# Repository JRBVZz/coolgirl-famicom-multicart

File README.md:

# COOLGIRL - ultimate multigame cartridge for Famicom

The goal of the project is to create a open source Famicom cartridge that will not be too expensive and can contain up to ~700 games of various mappers.

It's inspired by ultra cheap "COOLBOY" multicarts but instead of using single mapper (MMC3) "COOLGIRL" uses EPM1270T144 CPLD chip to simulate many different mappers. Both PRG and CHR data stored on a single flash memory chip. Before game starts loader loads CHR data from flash to CHR RAM and sets PRG offset, banking modes, mapper code and other settings via registers. There is lockout register bit which prevents further writes.

Full characteristics:
* PRG ROM: up to 128 MiB
* CHR RAM: up to 512 KiB
* PRG RAM: 32 KiB, non-volatile (FRAM) (optional)

--> You can use FRAM or SRAM with Battery. If you select FRAM (18W08 or 18L08), just solder jumper "FRAM". With SRAM (e.g. CY62256VLL)+Battery you need solder D2, D3, R4.
## How to build
### Hardware - KiCad 8 Version
#### Bill of materials
Dowload [BoM](CoolGirl_rev6.4-KiCad/Coolgirl-iBOM.html) and use interactive map.

#### Schematic
[Schematic](CoolGirl_rev6.4-KiCad/CG-Schematic.jpg) picture

The [source file](CoolGirl_rev6.4-KiCad/Coolgirl.kicad_sch) can be opened using the [KiCad 8](https://www.kicad.org/).

#### Board
Board designed for order on [jlcpcb.com](https://jlcpcb.com).

* Layers: 2
* PCB Thickness: 1.2mm
* Golden fingers highly recommended

The [source file](CoolGirl_rev6.4-KiCad/Coolgirl.kicad_pcb) can be opened using the [KiCad 8](https://www.kicad.org/).

### Firmware
EPM1270T144 CPLD firmware can be compiled using the [Quartus 22.1](https://www.intel.com/content/www/us/en/collections/products/fpga/software/downloads.html?s=Newest&f:guidetm83741EA404664A899395C861EDA3D38B=%5BIntel%C2%AE%20MAX%C2%AE%20CPLDs%20and%20FPGAs%3BMAX%C2%AE%20II%20CPLDs%5D). Open [CoolGirl.qpf](CoolGirl_rev6.x/CoolGirl.qpf) to configure and compile project.

All mappers can't fit into the CPLD at once, so you need to select required mappers in (config file)[CoolGirl_config.vh], so they can fit into 1270 macrocells. Also, you can set RESET_COMBINATION parameter to specify software reset button combination, it works on original consoles and some famiclones. Default combination is 8'b11010010 (Left+Start+A+B). Set it to 0 to disable and free some macrocells.

There are JTAG pads on the cartridge board to connect programmer (USB Blaster).

### ROM preparing
You can use [COOLGIRL Multirom Builder](https://github.com/ClusterM/coolgirl-multirom-builder) to combine multiple ROMs into one with menu and loader. ROM can be written to assembled cartridge using [Famicom/NES Dumper/Writer](https://github.com/ClusterM/famicom-dumper-writer). Non-soldered flash memory chip can be written using programmer.

## Registers
Range: $5000-$5FFF

Mask: $5007

All registers are $00 on power-on and reset.

### $5xx0
```
 7  bit  0
 ---- ----
 PPPP PPPP
 |||| ||||
 ++++-++++-- PRG base offset (A29-A22)
```

### $5xx1
```
 7  bit  0
 ---- ----
 PPPP PPPP
 |||| ||||
 ++++-++++-- PRG base offset (A21-A14)
```

### $5xx2
```
 7  bit  0
 ---- ----
 AMMM MMMM
 |||| ||||
 |+++-++++-- PRG mask (A20-A14, inverted+anded with PRG address)
 +---------- CHR mask (A18, inverted+anded with CHR address)
```

### $5xx3
```
 7  bit  0
 ---- ----
 BBBC CCCC
 |||| ||||
 |||+-++++-- CHR bank A (bits 7-3)
 +++-------- PRG banking mode (see below)
```

### $5xx4
```
 7  bit  0
 ---- ----
 DDDE EEEE
 |||| ||||
 |||+-++++-- CHR mask (A17-A13, inverted+anded with CHR address)
 +++-------- CHR banking mode (see below)
```

### $5xx5
```
 7  bit  0
 ---- ----
 CDDE EEWW
 |||| ||||
 |||| ||++-- 8KiB WRAM page at $6000-$7FFF
 |+++-++---- PRG bank A (bits 5-1)
 +---------- CHR bank A (bit 8)
```

### $5xx6
```
 7  bit  0
 ---- ----
 FFFM MMMM
 |||| ||||
 |||+ ++++-- Mapper code (bits 4-0, see below)
 +++-------- Flags 2-0, functionality depends on selected mapper
```

### $5xx7
```
 7  bit  0
 ---- ----
 LMTR RSNO
 |||| |||+-- Enable WRAM (read and write) at $6000-$7FFF
 |||| ||+--- Allow writes to CHR RAM
 |||| |+---- Allow writes to flash chip
 |||+-+----- Mirroring (00=vertical, 01=horizontal, 10=1Sa, 11=1Sb)
 ||+-------- Enable four-screen mode
 |+-- ------ Mapper code (bit 5, see below)
 +---------- Lockout bit (prevent further writes to all registers)
```

## Mapper codes
```
| Code   | iNES mapper number(s) and name(s)  | Flags meaning                         | Notes                                     |
| ====== + ================================== + ===================================== + ========================================= |
| 000000 | 0 (NROM) †                         |                                       |                                           |
| ------ + ---------------------------------- + ------------------------------------- + ----------------------------------------- |
| 000001 | 2 (UxROM) †                        | 0 - enable "Fire Hawk" mirroring for  | Mapper 2 is fully compartible with mapper |
|        | 71 (Codemasters) *                 |     mapper 71 (Codemasters)           | 71 but "Fire Hawk" only uses mirroring    |
|        | 30 (UNROM-512)                     | 1 - Enable one screen mirroring       | control. UNROM-512 self-writable feature  |
|        |                                    |     select for mapper 30 (UNROM-512)  | is not supported                          |
| ------ + ---------------------------------- + ------------------------------------- + ----------------------------------------- |
| 000010 | 3 (CNROM) †                        |                                       |                                           |
| ------ + ---------------------------------- + ------------------------------------- + ----------------------------------------- |
| 000011 | 78 (Irem) *                        |                                       |                                           |
| ------ + ---------------------------------- + ------------------------------------- + ----------------------------------------- |
| 000100 | 97 (Irem's TAM-S1)                 |                                       |                                           |
| ------ + ---------------------------------- + ------------------------------------- + ----------------------------------------- |
| 000101 | 93 (Sunsoft-2) *                   |                                       |                                           |
| ------ + ---------------------------------- + ------------------------------------- + ----------------------------------------- |
| 000110 | 163 (Nanjing)                      |                                       |                                           |
| ------ + ---------------------------------- + ------------------------------------- + ----------------------------------------- |
| 000111 | 18 (Jaleco SS 88006)               |                                       |                                           |
| ------ + ---------------------------------- + ------------------------------------- + ----------------------------------------- |
| 001000 | 7 (AxROM) †                        | 0 - disable mirroring control, used   | Can be oversized to 512 KiB.              |
|        | 34 (BNROM, NINA-001) *             |     to select mapper 34 instead of 7  | iNES Mapper 034 is used to designate both |
|        |                                    |                                       | the BNROM and NINA-001 boards but only    |
|        |                                    |                                       | BNROM is supported                        |
| ------ + ---------------------------------- + ------------------------------------- + ----------------------------------------- |
| 001001 | 228 (Action 52)                    |                                       | Only Cheetahmen II is supported           |
| ------ + ---------------------------------- + ------------------------------------- + ----------------------------------------- |
| 001010 | 11 (Color Dreams) *                |                                       |                                           |
| ------ + ---------------------------------- + ------------------------------------- + ----------------------------------------- |
| 001011 | 66 (GxROM) *                       |                                       |                                           |
| ------ + ---------------------------------- + ------------------------------------- + ----------------------------------------- |
| 001100 | 87 *                               |                                       |                                           |
| ------ + ---------------------------------- + ------------------------------------- + ----------------------------------------- |
| 001101 | 90 (J.Y. Company) *                |                                       | Partial support only, can be used for     |
|        |                                    |                                       | "Aladdin" and "Super Mario World" only.   |
|        |                                    |                                       | "Super Mario World" requires to enable    |
|        |                                    |                                       | accurate IRQs and multiplier (disabled by |
|        |                                    |                                       | default)                                  |
| ------ + ---------------------------------- + ------------------------------------- + ----------------------------------------- |
| 001110 | 65 (Irem's H3001) *                |                                       |                                           |
| ------ + ---------------------------------- + ------------------------------------- + ----------------------------------------- |
| 001111 | 5 (MMC5) *                         |                                       | Experimental partically support, can be   |
|        |                                    |                                       | used for "Castlevania 3 (U)" only         |
| ------ + ---------------------------------- + ------------------------------------- + ----------------------------------------- |
| 010000 | 1 (MMC1) †                         | 0 - enable 16KiB of WRAM              |                                           |
| ------ + ---------------------------------- + ------------------------------------- + ----------------------------------------- |
| 010001 | 9 (MMC2) *                         |                                       |                                           |
|        | 10 (MMC4) *                        | 0 - 0=MMC2, 1=MMC4                    |                                           |
| ------ + ---------------------------------- + ------------------------------------- + ----------------------------------------- |
| 010010 | 70 *                               | 0 - 0=70, 1=152                       |                                           |
|        | 152 *                              |                                       |                                           |
| ------ + ---------------------------------- + ------------------------------------- + ----------------------------------------- |
| 010011 | 73 (VRC3)                          |                                       |                                           |
| ------ + ---------------------------------- + ------------------------------------- + ----------------------------------------- |
| 010100 | 4 (MMC3/MMC6) †                    | 0 - use mapper 118 (TxROM)            | Can be oversized up to 2 MiB              |
|        | 118 (TxROM) *                      | 1 - use mapper 189                    |                                           |
|        | 189 *                              | 2 - use mapper 206                    |                                           |
|        | 206 (Namco, Tengen, others)        |                                       |                                           |
| ------ + ---------------------------------- + ------------------------------------- + ----------------------------------------- |
| 010101 | 112                                |                                       |                                           |
| ------ + ---------------------------------- + ------------------------------------- + ----------------------------------------- |
| 010110 | 33 (Taito) *                       | 0 - 0=33, 1=48                        |                                           |
|        | 48 (Taito) *                       |                                       |                                           |
| ------ + ---------------------------------- + ------------------------------------- + ----------------------------------------- |
| 010111 | 42 (FDS conversions) *             |                                       | Interrupts disabled by default            |
| ------ + ---------------------------------- + ------------------------------------- + ----------------------------------------- |
| 011000 | 21 (VRC2/VRC4) *                   | 2,0 - A0 and A1 lines configuration:  |                                           |
|        | 22 (VRC2/VRC4) *                   |     0,0 - like mapper 21              |                                           |
|        | 23 (VRC2/VRC4) *                   |     0,1 - like mapper 22              |                                           |
|        | 25 (VRC2/VRC4) *                   |     1,0 - like mapper 23              |                                           |
|        |                                    |     1,1 - like mapper 25              |                                           |
|        |                                    | 1 - divide CHR bank select by two     |                                           |
|        |                                    |     (VRC2a, mapper 22)                |                                           |
| ------ + ---------------------------------- + ------------------------------------- + ----------------------------------------- |
| 011001 | 69 (Sunsoft FME-7) *               |                                       |                                           |
| ------ + ---------------------------------- + ------------------------------------- + ----------------------------------------- |
| 011010 | 32 (IREM G-101) *                  |                                       |                                           |
| ------ + ---------------------------------- + ------------------------------------- + ----------------------------------------- |
| 011011 | 79 (NINA-03/06)                    |                                       |                                           |
|        | 146 (Sachen 3015)                  |                                       |                                           |
| ------ + ---------------------------------- + ------------------------------------- + ----------------------------------------- |
| 011100 | 133 (Sachen)                       |                                       |                                           |
| ------ + ---------------------------------- + ------------------------------------- + ----------------------------------------- |
| 011101 | 36 (TXC's PCB 01-22000-400)        |                                       |                                           |
| ------ + ---------------------------------- + ------------------------------------- + ----------------------------------------- |
| 011110 | Reserved                           |                                       |                                           |
| ------ + ---------------------------------- + ------------------------------------- + ----------------------------------------- |
| 011111 | 184 (Sunsoft-1)                    |                                       |                                           |
| ------ + ---------------------------------- + ------------------------------------- + ----------------------------------------- |
| 100000 | 38                                 |                                       |                                           |
| ------ + ---------------------------------- + ------------------------------------- + ----------------------------------------- |
| 100001 | Reserved                           |                                       |                                           |
| ------ + ---------------------------------- + ------------------------------------- + ----------------------------------------- |
| 100010 | 75 (VRC1)                          |                                       |                                           |
| ------ + ---------------------------------- + ------------------------------------- + ----------------------------------------- |
| 100011 | 83                                 | 0 - DIP switch 0                      | Partial support, submapper 1 requires     |
|        |                                    | 1 - DIP switch 1                      | 512 KiB of CHR RAM                        |
|        |                                    | 2 - use submapper 1                   |                                           |
| ------ + ---------------------------------- + ------------------------------------- + ----------------------------------------- |
| 100100 | 67 (Sunsoft-3)                     |                                       |                                           |
| ------ + ---------------------------------- + ------------------------------------- + ----------------------------------------- |
| 100101 | 89 (Sunsoft-2 on Sunsoft-3 PCB)    |                                       |                                           |
| ------ + ---------------------------------- + ------------------------------------- + ----------------------------------------- |
| ...... | Reserved                           |                                       |                                           |

† - very popular mappers, can't be disabled in config
* - enabled by default in config
```

## PRG banking modes
```
| Code | $8000 | $A000 | $E000 | $C000 | Notes                                    |
| ==== + ===== + ===== + ===== + ===== + ======================================== |
| 000  |       A       |       C       | UxROM, MMC4, MMC1 mode #3, etc.          |
| ---- + ------------- + ------------- + ---------------------------------------- |
| 001  |       C       |       A       | Mapper 97 (TAM-S1)                       |
| ---- + ------------- + ------------- + ---------------------------------------- |
| 010  |           Reserved            |                                          |
| ---- + ----------------------------- + ---------------------------------------- |
| 011  |           Reserved            |                                          |
| ---- + ----- + ----- + ----- + ----- + ---------------------------------------- |
| 100  |   A   |   B   |   C   |   D   | Universal, used by MMC3 mode 0, etc.     |
| ---- + ----- + ----- + ----- + ----- + ---------------------------------------- |
| 101  |   C   |   B   |   A   |   D   | MMC3 mode 1                              |
| ---- + ----- + ----- + ----- + ----- + ---------------------------------------- |
| 110  |               B               | Mapper 163                               |
| ---- + ----------------------------- + ---------------------------------------- |
| 111  |               A               | AxROM, MMC1 modes 0/1, Color Dreams      |
```
Power-on/reset state: A=0, B=~2, C=~1, D=~0

## CHR banking modes
```
| Code | $0000 | $0400 | $0800 | $0C00 | $1000 | $1400 | $1800 | $1C00 | Notes                                    |
| ==== + ===== + ===== + ===== + ===== + ===== + ===== + ===== + ===== + ======================================== |
| 000  |                               A                               | Used by many simple mappers              |
| ---- + ------------------------------------------------------------- + ---------------------------------------- |
| 001  |                          Spetial mode                         | Used by mapper 163                       |
| ---- + ----- + ----- + ----- + ----- + ----- + ----- + ----- + ----- + ---------------------------------------- |
| 010  |       A       |       C       |   E   |   F   |   G   |   H   | Used by MMC3 mode 0                      |
| ---- + ----- + ----- + ----- + ----- + ----- + ----- + ----- + ----- + ---------------------------------------- |
| 011  |   E   |   F   |   G   |   H   |       A       |       C       | Used by MMC3 mode 1                      |
| ---- + ----- + ----- + ----- + ----- + ------------- + ------------- + ---------------------------------------- |
| 100  |               A               |               E               | Used by MMC1                             |
| ---- + ----------------------------- + ------------- + ------------- + ---------------------------------------- |
| 101  |              A/B              |              E/F              | MMC2/MMC4, switched by tiles $FD or $FE  |
| ---- + ------- ----- + ------------- + ------------- + ------------- + ---------------------------------------- |
| 110  |       A       |       C       |       E       |       G       | Used by many complicated mappers         |
| ---- + ----- + ----- + ----- + ----- + ----- + ----- + ----- + ----- + ---------------------------------------- |
| 111  |   A   |   B   |   C   |   D   |   E   |  F    |   G   |   H   | Used by very complicated mappers         |
```
Power-on/reset state: A=0, B=1, C=2, D=3, E=4, F=5, G=6, H=7

## Donate
* PayPal: cluster@cluster.wtf
* [Donation Alerts](https://www.donationalerts.com/r/clustermeerkat)
* [Boosty](https://boosty.to/cluster)

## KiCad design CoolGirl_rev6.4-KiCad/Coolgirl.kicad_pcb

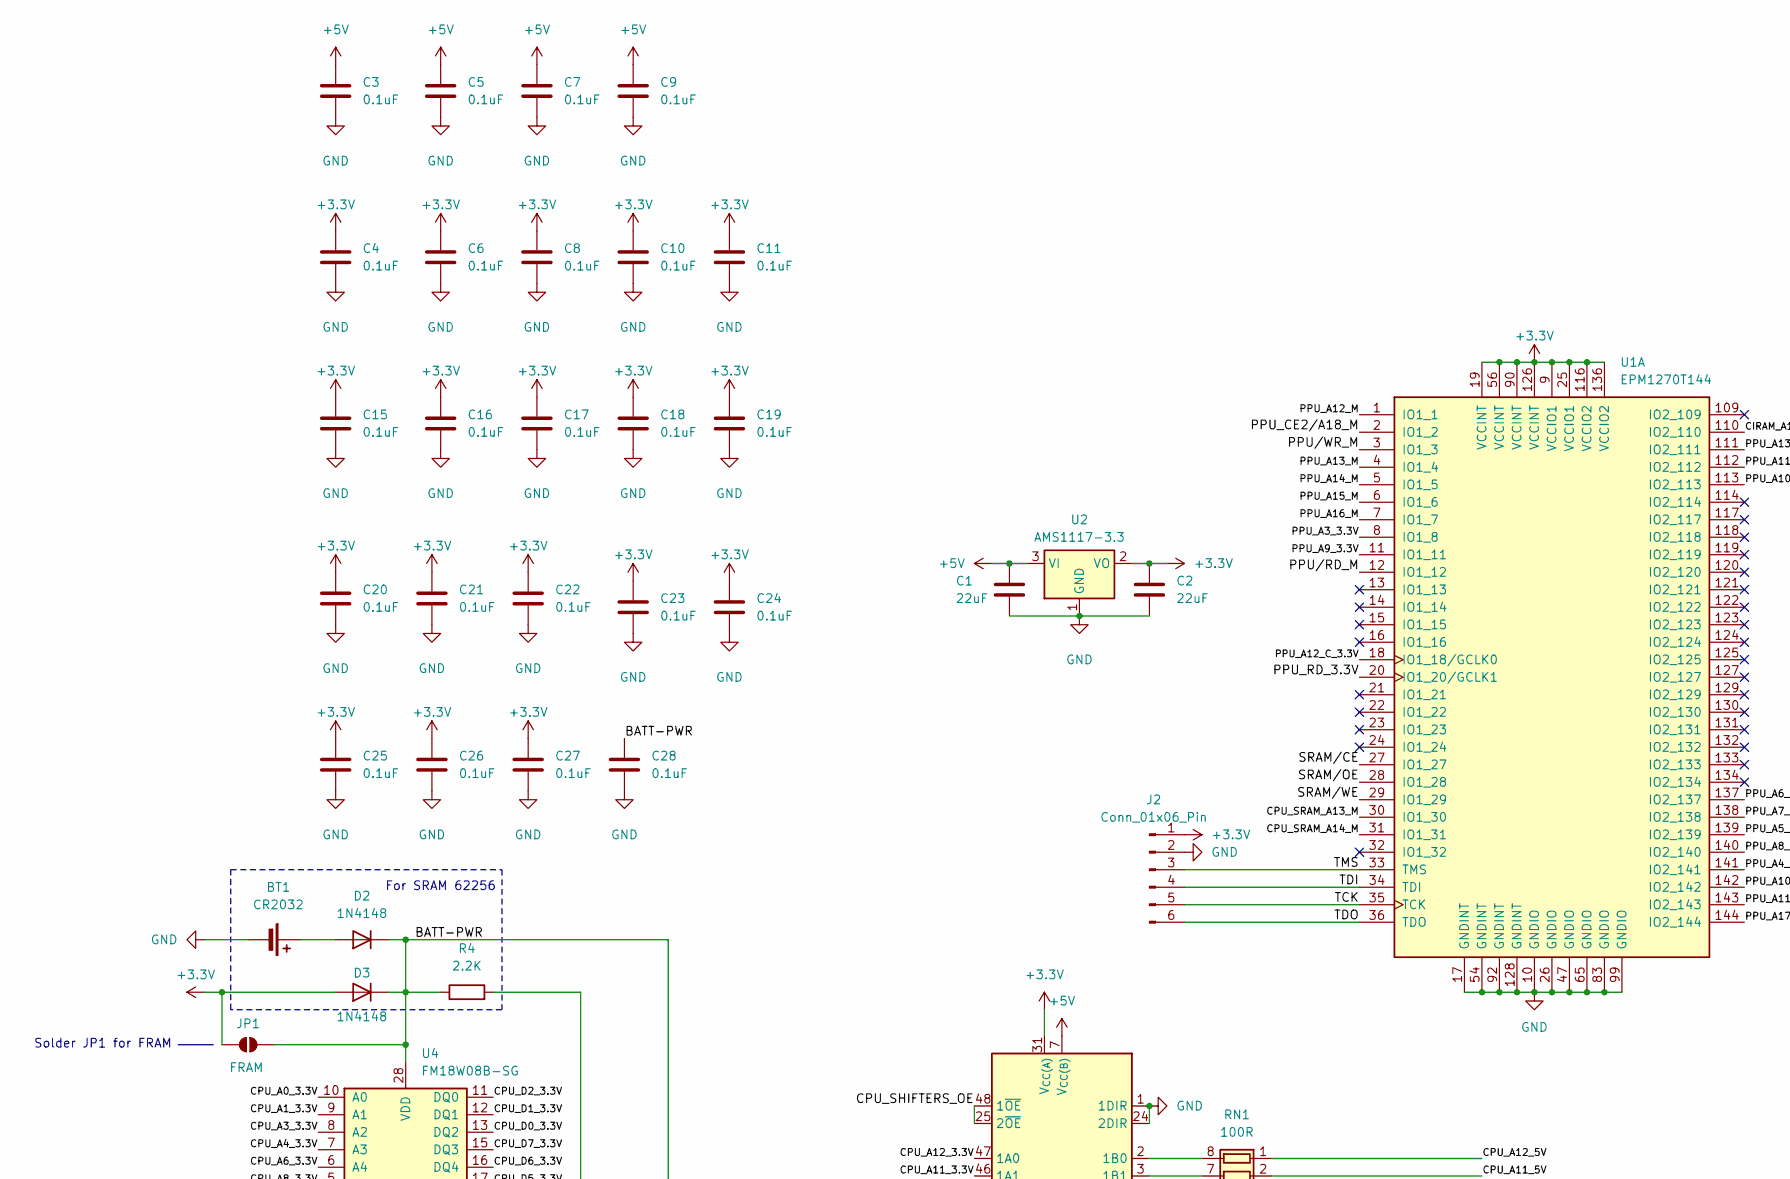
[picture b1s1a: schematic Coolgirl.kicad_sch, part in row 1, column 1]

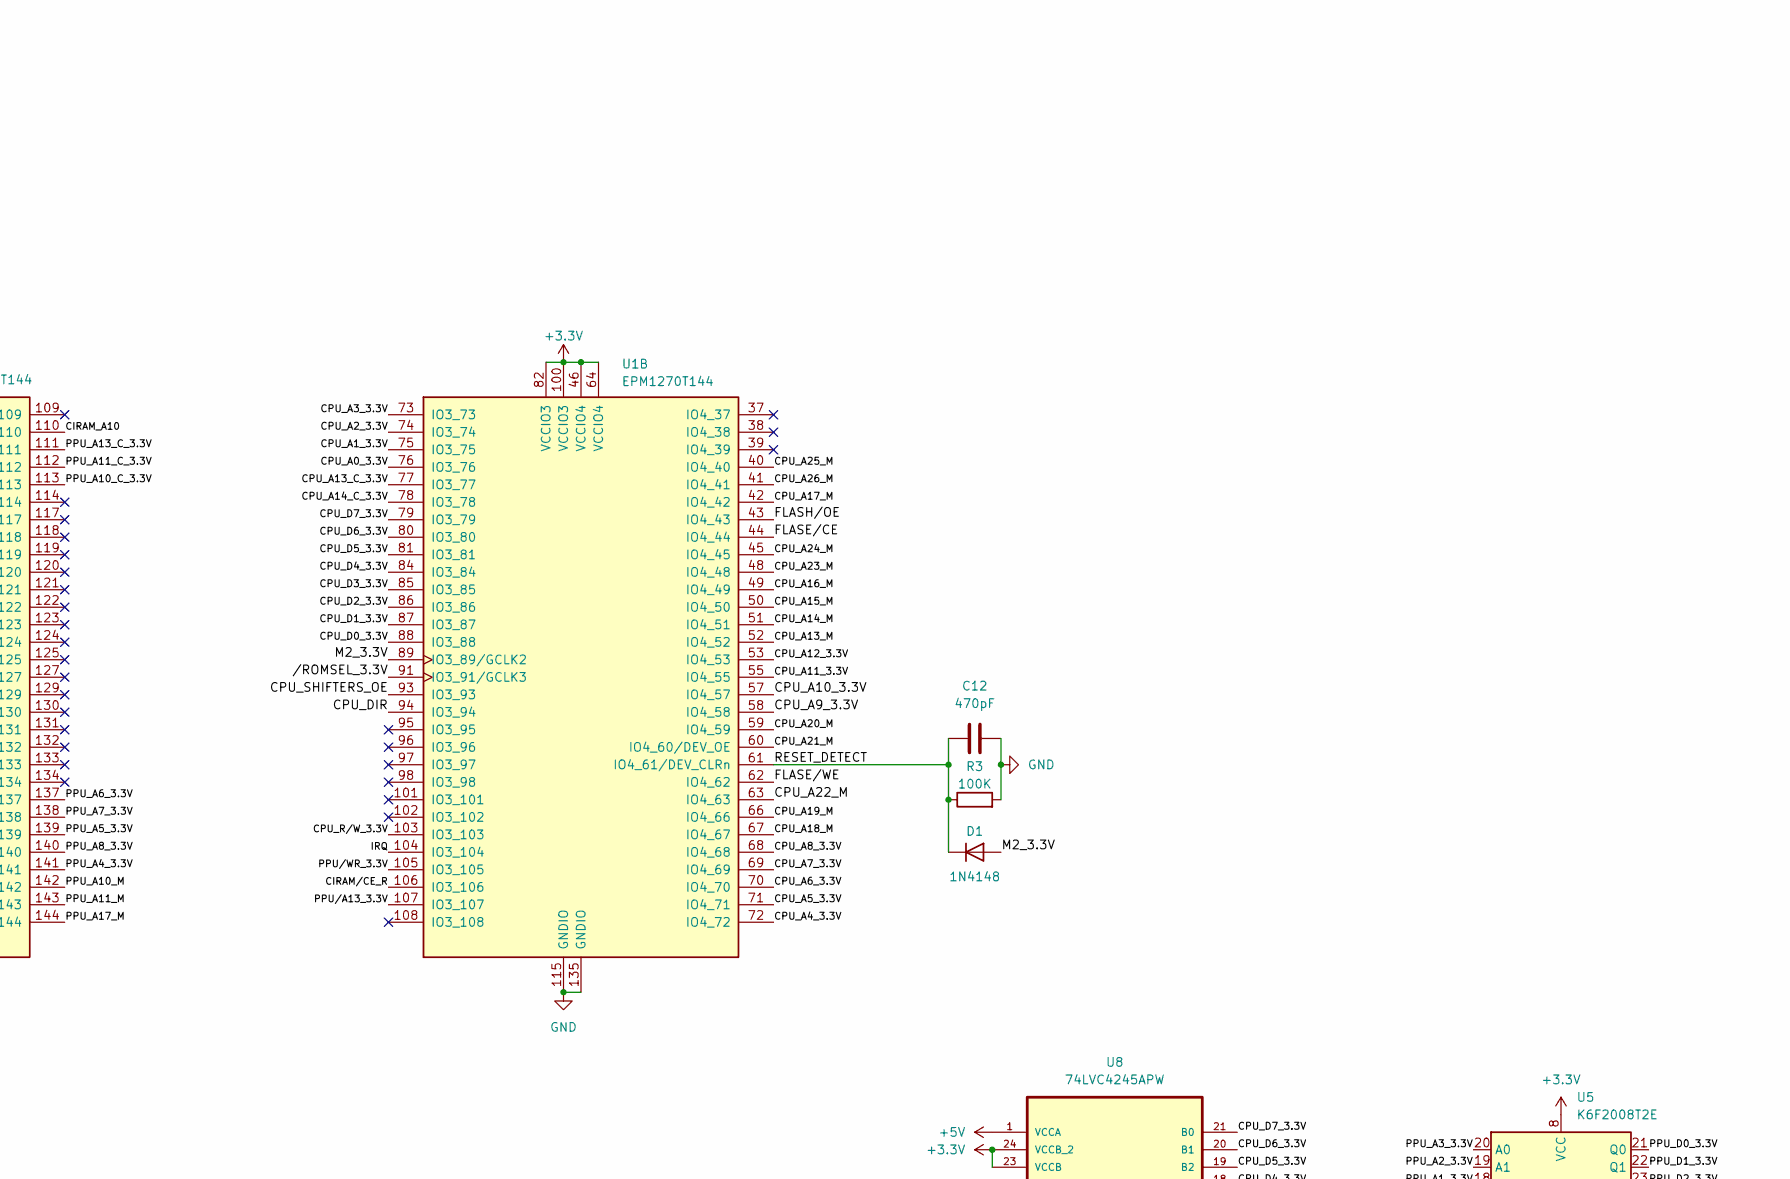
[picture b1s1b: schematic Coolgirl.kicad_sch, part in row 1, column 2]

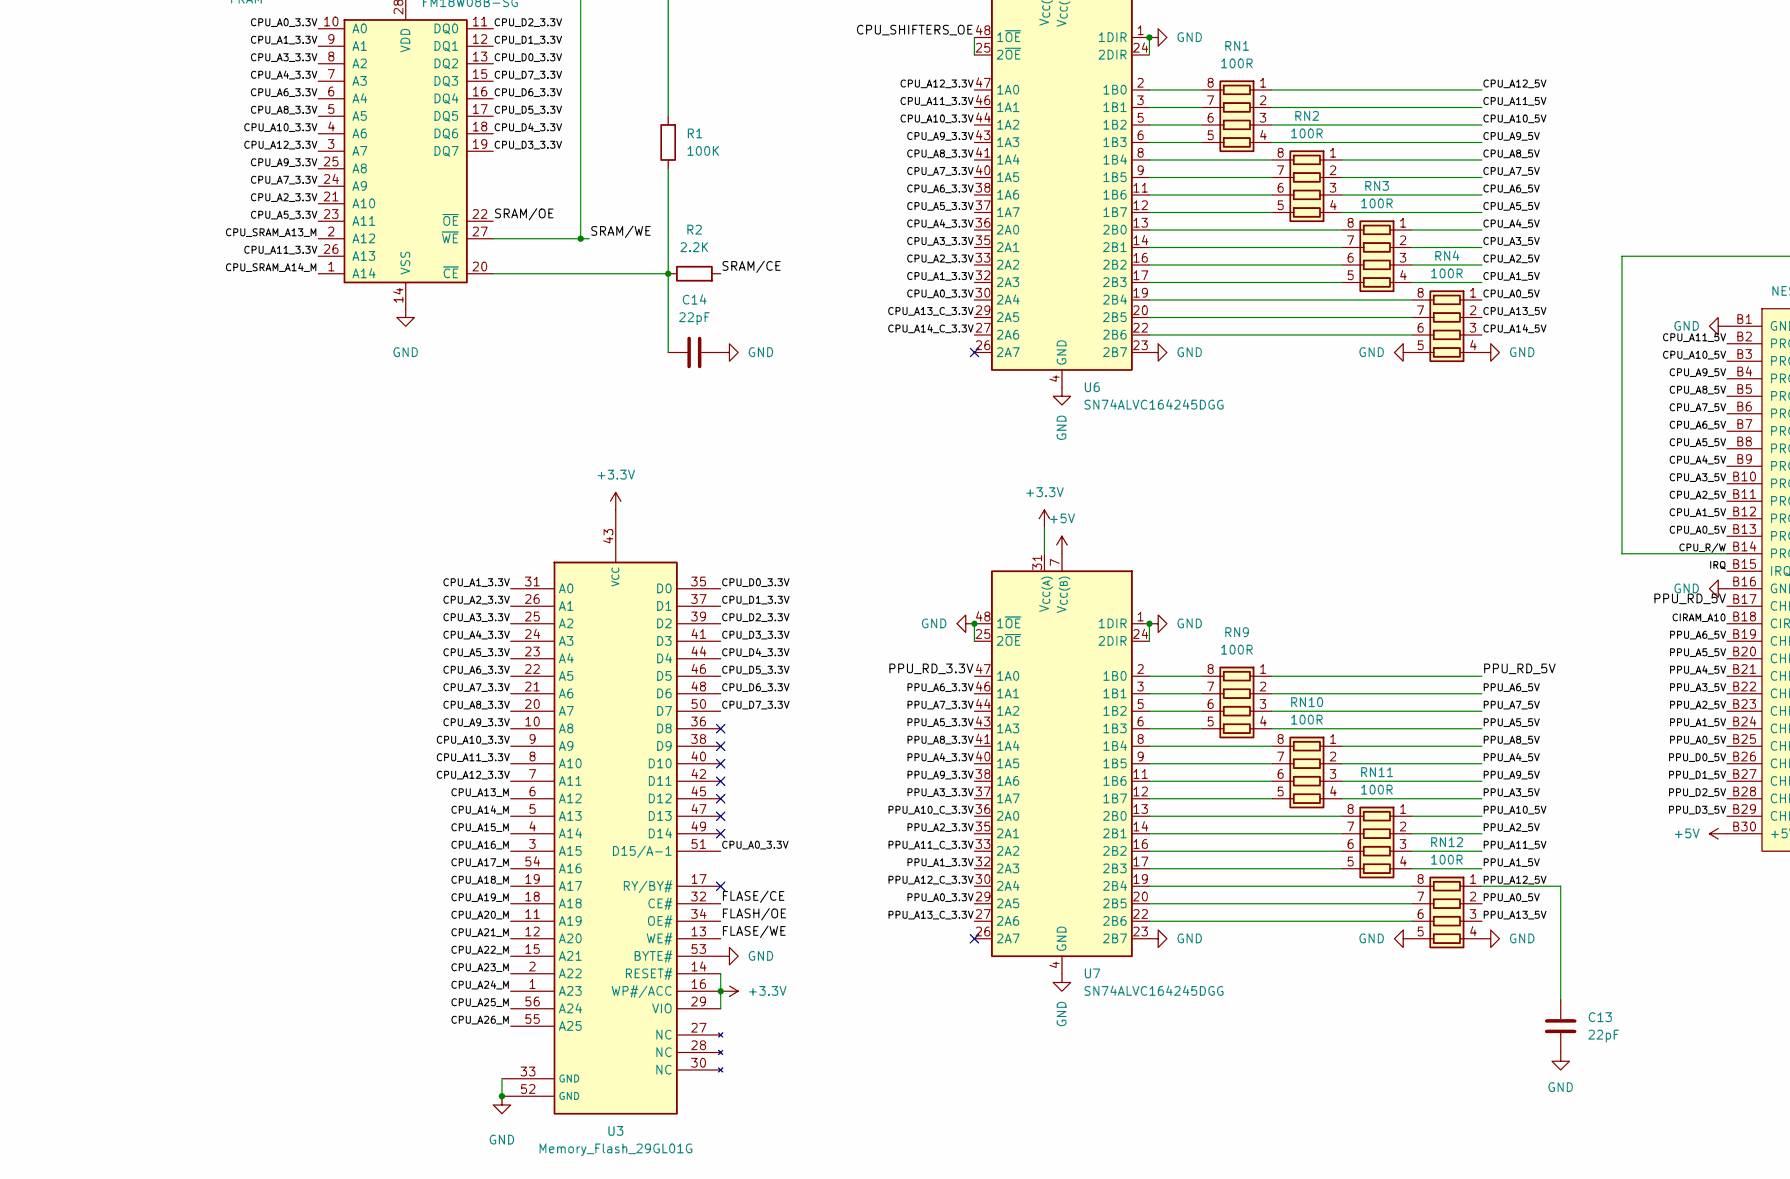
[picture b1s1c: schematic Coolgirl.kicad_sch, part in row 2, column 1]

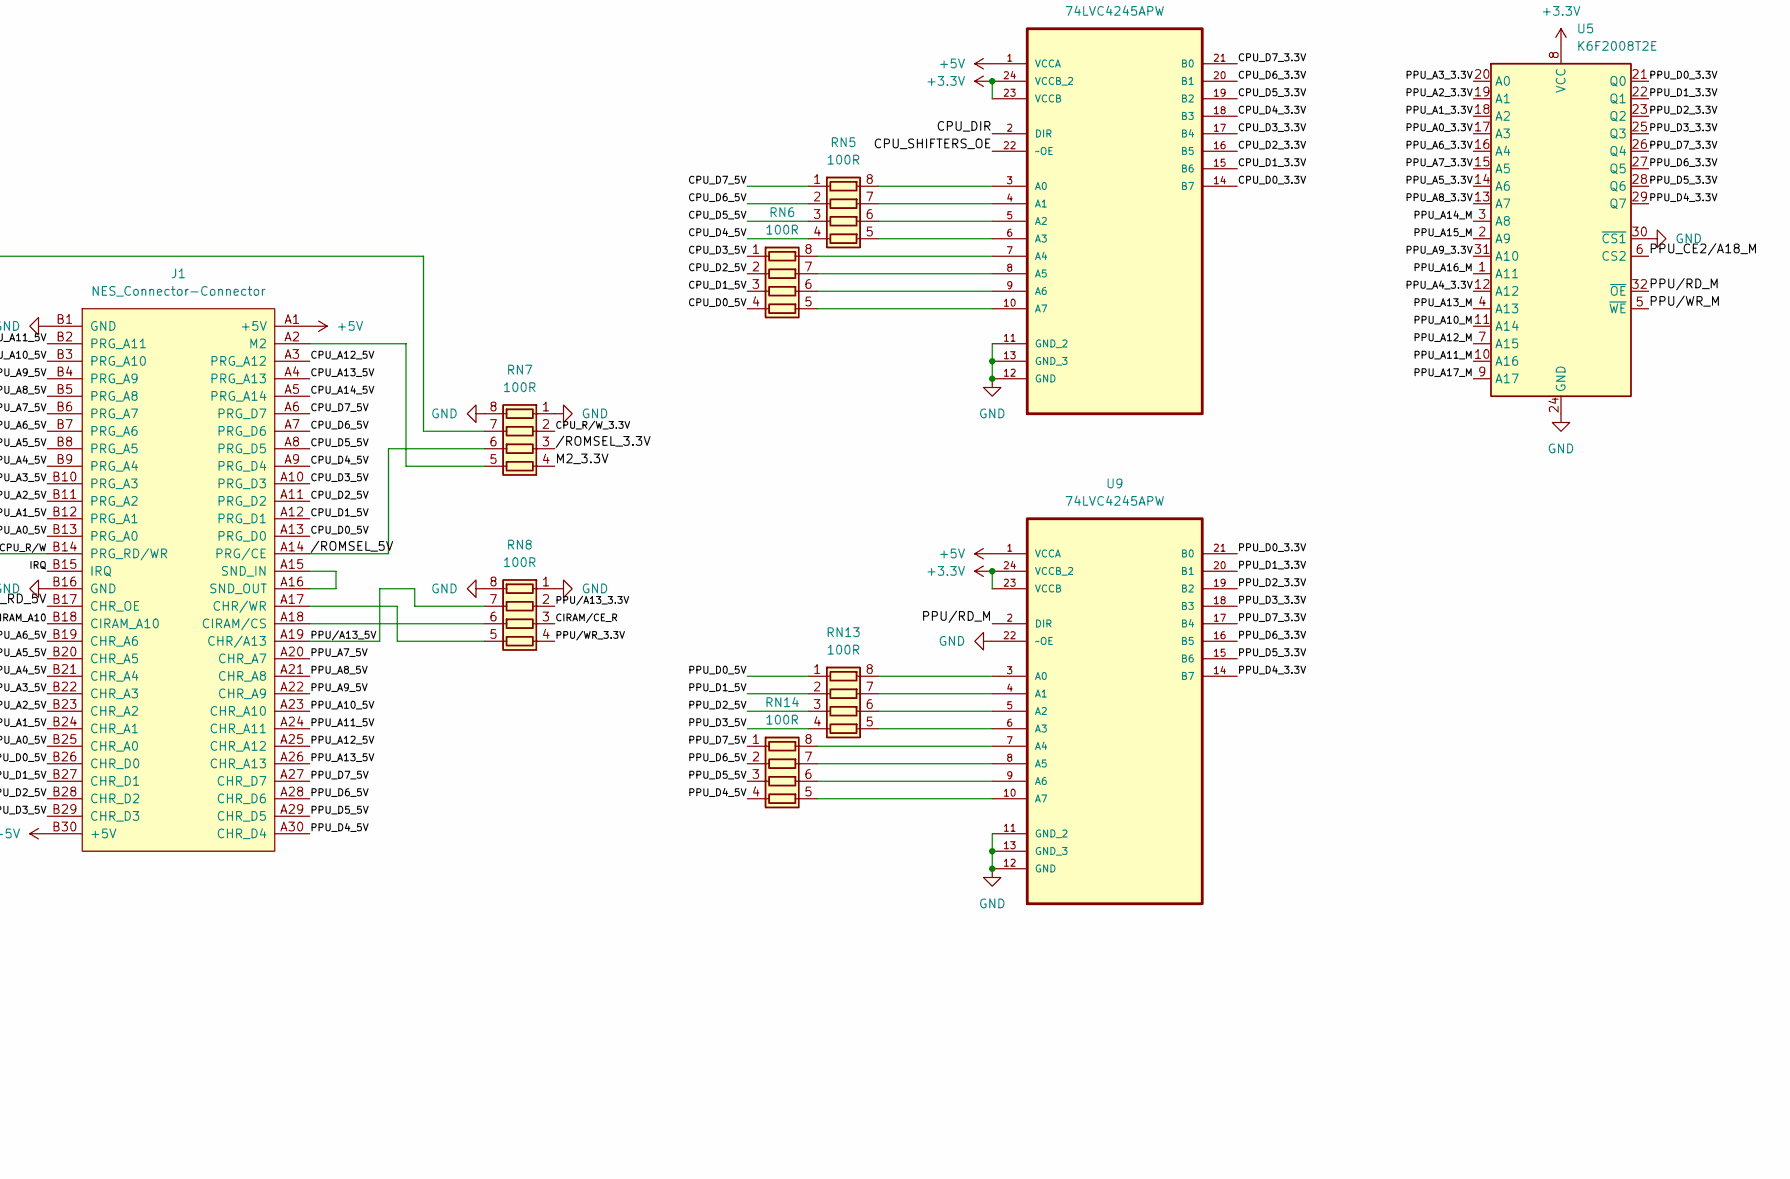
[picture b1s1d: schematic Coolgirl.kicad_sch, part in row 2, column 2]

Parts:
BT1: CR2032; BatteryHolder_Keystone_1060_1x2032
C1, C2: 22uF; C_0805_2012Metric
C3, C4, C5, C6, C7, C8, C9, C10, C11, C15, C16, C17, C18, C19, C20, C21, C22, C23, C24, C25, C26, C27, C28: 0.1uF; C_0603_1608Metric_Pad1.08x0.95mm_HandSolder
C12: 470pF; C_0805_2012Metric
C13, C14: 22pF; C_0805_2012Metric
D1, D2, D3: 1N4148; D_SOD-123
J1: NES_Connector-Connector; NES_Connector
J2: Conn_01x06_Pin; PinHeader_1x06_P2.54mm_Vertical
JP1: FRAM; SolderJumper-2_P1.3mm_Open_RoundedPad1.0x1.5mm
R1, R3: 100K; R_0805_2012Metric
R2, R4: 2.2K; R_0805_2012Metric
RN1, RN2, RN3, RN4, RN5, RN6, RN7, RN8, RN9, RN10, RN11, RN12, RN13, RN14: 100R; R_Array_Convex_4x0603
U1: EPM1270T144; LQFP-144_20x20mm_P0.5mm
U2: AMS1117-3.3; SOT-223-3_TabPin2
U3: Memory_Flash_29GL01G; TSOP-I-56_18.4x14mm_P0.5mm
U4: FM18W08B-SG; SOP-28
U5: K6F2008T2E; TSOP-I-32_11.8-18.4x8mm_P0.5mm
U6, U7: SN74ALVC164245DGG; TSSOP-48_6.1x12.5mm_P0.5mm
U8, U9: 74LVC4245APW; TSSOP-24_4.4x7.8mm_P0.65mm

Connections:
+3.3V: C2.1, C4.1, C6.1, C8.1, C10.1, C11.1, C15.1, C16.1, C17.1, C18.1, C19.1, C20.1, C21.1, C22.1, C23.1, C24.1, C25.1, C26.1, C27.1, D3.2 (A), J2.1, JP1.1 (A), U1.9 (VCCIO1), U1.19 (VCCINT), U1.25 (VCCIO1), U1.46 (VCCIO4), U1.56 (VCCINT), U1.64 (VCCIO4), U1.82 (VCCIO3), U1.90 (VCCINT), U1.100 (VCCIO3), U1.116 (VCCIO2), U1.126 (VCCINT), U1.136 (VCCIO2), U2.2 (VO), U3.14 (RESET#), U3.16 (WP#/ACC), U3.29 (VIO), U3.43 (VCC), U5.8 (VCC), U6.31 (V_{CC(A)}), U6.42 (V_{CC(A)}), U7.31 (V_{CC(A)}), U7.42 (V_{CC(A)}), U8.23 (VCCB), U8.24 (VCCB_2), U9.23 (VCCB), U9.24 (VCCB_2)
+5V: C1.1, C3.1, C5.1, C7.1, C9.1, J1.A1 (+5V), J1.B30 (+5V), U2.3 (VI), U6.7 (V_{CC(B)}), U6.18 (V_{CC(B)}), U7.7 (V_{CC(B)}), U7.18 (V_{CC(B)}), U8.1 (VCCA), U9.1 (VCCA)
/BATT-PWR: C28.1, D2.1 (K), D3.1 (K), JP1.2 (B), R1.2, R4.1, U4.28 (VDD)
/CIRAM_A10: J1.B18 (CIRAM_A10), U1.110 (IO2_110)
/CIRAM/CE_R: RN8.3 (R3.1), U1.106 (IO3_106)
/CPU_A0_3.3V: U1.76 (IO3_76), U3.51 (D15/A-1), U4.10 (A0), U6.30 (2A4)
/CPU_A0_5V: J1.B13 (PRG_A0), RN4.1 (R1.1)
/CPU_A1_3.3V: U1.75 (IO3_75), U3.31 (A0), U4.9 (A1), U6.32 (2A3)
/CPU_A1_5V: J1.B12 (PRG_A1), RN3.4 (R4.1)
/CPU_A2_3.3V: U1.74 (IO3_74), U3.26 (A1), U4.21 (A10), U6.33 (2A2)
/CPU_A2_5V: J1.B11 (PRG_A2), RN3.3 (R3.1)
/CPU_A3_3.3V: U1.73 (IO3_73), U3.25 (A2), U4.8 (A2), U6.35 (2A1)
/CPU_A3_5V: J1.B10 (PRG_A3), RN3.2 (R2.1)
/CPU_A4_3.3V: U1.72 (IO4_72), U3.24 (A3), U4.7 (A3), U6.36 (2A0)
/CPU_A4_5V: J1.B9 (PRG_A4), RN3.1 (R1.1)
/CPU_A5_3.3V: U1.71 (IO4_71), U3.23 (A4), U4.23 (A11), U6.37 (1A7)
/CPU_A5_5V: J1.B8 (PRG_A5), RN2.4 (R4.1)
/CPU_A6_3.3V: U1.70 (IO4_70), U3.22 (A5), U4.6 (A4), U6.38 (1A6)
/CPU_A6_5V: J1.B7 (PRG_A6), RN2.3 (R3.1)
/CPU_A7_3.3V: U1.69 (IO4_69), U3.21 (A6), U4.24 (A9), U6.40 (1A5)
/CPU_A7_5V: J1.B6 (PRG_A7), RN2.2 (R2.1)
/CPU_A8_3.3V: U1.68 (IO4_68), U3.20 (A7), U4.5 (A5), U6.41 (1A4)
/CPU_A8_5V: J1.B5 (PRG_A8), RN2.1 (R1.1)
/CPU_A9_3.3V: U1.58 (IO4_58), U3.10 (A8), U4.25 (A8), U6.43 (1A3)
/CPU_A9_5V: J1.B4 (PRG_A9), RN1.4 (R4.1)
/CPU_A10_3.3V: U1.57 (IO4_57), U3.9 (A9), U4.4 (A6), U6.44 (1A2)
/CPU_A10_5V: J1.B3 (PRG_A10), RN1.3 (R3.1)
/CPU_A11_3.3V: U1.55 (IO4_55), U3.8 (A10), U4.26 (A13), U6.46 (1A1)
/CPU_A11_5V: J1.B2 (PRG_A11), RN1.2 (R2.1)
/CPU_A12_3.3V: U1.53 (IO4_53), U3.7 (A11), U4.3 (A7), U6.47 (1A0)
/CPU_A12_5V: J1.A3 (PRG_A12), RN1.1 (R1.1)
/CPU_A13_5V: J1.A4 (PRG_A13), RN4.2 (R2.1)
/CPU_A13_C_3.3V: U1.77 (IO3_77), U6.29 (2A5)
/CPU_A13_M: U1.52 (IO4_52), U3.6 (A12)
/CPU_A14_5V: J1.A5 (PRG_A14), RN4.3 (R3.1)
/CPU_A14_C_3.3V: U1.78 (IO3_78), U6.27 (2A6)
/CPU_A14_M: U1.51 (IO4_51), U3.5 (A13)
/CPU_A15_M: U1.50 (IO4_50), U3.4 (A14)
/CPU_A16_M: U1.49 (IO4_49), U3.3 (A15)
/CPU_A17_M: U1.42 (IO4_42), U3.54 (A16)
/CPU_A18_M: U1.67 (IO4_67), U3.19 (A17)
/CPU_A19_M: U1.66 (IO4_66), U3.18 (A18)
/CPU_A20_M: U1.59 (IO4_59), U3.11 (A19)
/CPU_A21_M: U1.60 (IO4_60/DEV_OE), U3.12 (A20)
/CPU_A22_M: U1.63 (IO4_63), U3.15 (A21)
/CPU_A23_M: U1.48 (IO4_48), U3.2 (A22)
/CPU_A24_M: U1.45 (IO4_45), U3.1 (A23)
/CPU_A25_M: U1.40 (IO4_40), U3.56 (A24)
/CPU_A26_M: U1.41 (IO4_41), U3.55 (A25)
/CPU_D0_3.3V: U1.88 (IO3_88), U3.35 (D0), U4.13 (DQ2), U8.14 (B7)
/CPU_D0_5V: J1.A13 (PRG_D0), RN6.4 (R4.1)
/CPU_D1_3.3V: U1.87 (IO3_87), U3.37 (D1), U4.12 (DQ1), U8.15 (B6)
/CPU_D1_5V: J1.A12 (PRG_D1), RN6.3 (R3.1)
/CPU_D2_3.3V: U1.86 (IO3_86), U3.39 (D2), U4.11 (DQ0), U8.16 (B5)
/CPU_D2_5V: J1.A11 (PRG_D2), RN6.2 (R2.1)
/CPU_D3_3.3V: U1.85 (IO3_85), U3.41 (D3), U4.19 (DQ7), U8.17 (B4)
/CPU_D3_5V: J1.A10 (PRG_D3), RN6.1 (R1.1)
/CPU_D4_3.3V: U1.84 (IO3_84), U3.44 (D4), U4.18 (DQ6), U8.18 (B3)
/CPU_D4_5V: J1.A9 (PRG_D4), RN5.4 (R4.1)
/CPU_D5_3.3V: U1.81 (IO3_81), U3.46 (D5), U4.17 (DQ5), U8.19 (B2)
/CPU_D5_5V: J1.A8 (PRG_D5), RN5.3 (R3.1)
/CPU_D6_3.3V: U1.80 (IO3_80), U3.48 (D6), U4.16 (DQ4), U8.20 (B1)
/CPU_D6_5V: J1.A7 (PRG_D6), RN5.2 (R2.1)
/CPU_D7_3.3V: U1.79 (IO3_79), U3.50 (D7), U4.15 (DQ3), U8.21 (B0)
/CPU_D7_5V: J1.A6 (PRG_D7), RN5.1 (R1.1)
/CPU_DIR: U1.94 (IO3_94), U8.2 (DIR)
/CPU_R/W: J1.B14 (PRG_RD/WR), RN7.7 (R2.2)
/CPU_R/W_3.3V: RN7.2 (R2.1), U1.103 (IO3_103)
/CPU_SHIFTERS_OE: U1.93 (IO3_93), U6.25 (2~OE), U6.48 (1~OE), U8.22 (~OE)
/CPU_SRAM_A13_M: U1.30 (IO1_30), U4.2 (A12)
/CPU_SRAM_A14_M: U1.31 (IO1_31), U4.1 (A14)
/FLASE/CE: U1.44 (IO4_44), U3.32 (CE#)
/FLASE/WE: U1.62 (IO4_62), U3.13 (WE#)
/FLASH/OE: U1.43 (IO4_43), U3.34 (OE#)
/IRQ: J1.B15 (IRQ), U1.104 (IO3_104)
/M2_3.3V: D1.2 (A), RN7.4 (R4.1), U1.89 (IO3_89/GCLK2)
/PPU_A0_3.3V: U5.17 (A3), U7.29 (2A5)
/PPU_A0_5V: J1.B25 (CHR_A0), RN12.2 (R2.1)
/PPU_A1_3.3V: U5.18 (A2), U7.32 (2A3)
/PPU_A1_5V: J1.B24 (CHR_A1), RN11.4 (R4.1)
/PPU_A2_3.3V: U5.19 (A1), U7.35 (2A1)
/PPU_A2_5V: J1.B23 (CHR_A2), RN11.2 (R2.1)
/PPU_A3_3.3V: U1.8 (IO1_8), U5.20 (A0), U7.37 (1A7)
/PPU_A3_5V: J1.B22 (CHR_A3), RN10.4 (R4.1)
/PPU_A4_3.3V: U1.141 (IO2_141), U5.12 (A12), U7.40 (1A5)
/PPU_A4_5V: J1.B21 (CHR_A4), RN10.2 (R2.1)
/PPU_A5_3.3V: U1.139 (IO2_139), U5.14 (A6), U7.43 (1A3)
/PPU_A5_5V: J1.B20 (CHR_A5), RN9.4 (R4.1)
/PPU_A6_3.3V: U1.137 (IO2_137), U5.16 (A4), U7.46 (1A1)
/PPU_A6_5V: J1.B19 (CHR_A6), RN9.2 (R2.1)
/PPU_A7_3.3V: U1.138 (IO2_138), U5.15 (A5), U7.44 (1A2)
/PPU_A7_5V: J1.A20 (CHR_A7), RN9.3 (R3.1)
/PPU_A8_3.3V: U1.140 (IO2_140), U5.13 (A7), U7.41 (1A4)
/PPU_A8_5V: J1.A21 (CHR_A8), RN10.1 (R1.1)
/PPU_A9_3.3V: U1.11 (IO1_11), U5.31 (A10), U7.38 (1A6)
/PPU_A9_5V: J1.A22 (CHR_A9), RN10.3 (R3.1)
/PPU_A10_5V: J1.A23 (CHR_A10), RN11.1 (R1.1)
/PPU_A10_C_3.3V: U1.113 (IO2_113), U7.36 (2A0)
/PPU_A10_M: U1.142 (IO2_142), U5.11 (A14)
/PPU_A11_5V: J1.A24 (CHR_A11), RN11.3 (R3.1)
/PPU_A11_C_3.3V: U1.112 (IO2_112), U7.33 (2A2)
/PPU_A11_M: U1.143 (IO2_143), U5.10 (A16)
/PPU_A12_5V: C13.1, J1.A25 (CHR_A12), RN12.1 (R1.1)
/PPU_A12_C_3.3V: U1.18 (IO1_18/GCLK0), U7.30 (2A4)
/PPU_A12_M: U1.1 (IO1_1), U5.7 (A15)
/PPU_A13_5V: J1.A26 (CHR_A13), RN12.3 (R3.1)
/PPU_A13_C_3.3V: U1.111 (IO2_111), U7.27 (2A6)
/PPU_A13_M: U1.4 (IO1_4), U5.4 (A13)
/PPU_A14_M: U1.5 (IO1_5), U5.3 (A8)
/PPU_A15_M: U1.6 (IO1_6), U5.2 (A9)
/PPU_A16_M: U1.7 (IO1_7), U5.1 (A11)
/PPU_A17_M: U1.144 (IO2_144), U5.9 (A17)
/PPU_CE2/A18_M: U1.2 (IO1_2), U5.6 (CS2)
/PPU_D0_3.3V: U5.21 (Q0), U9.21 (B0)
/PPU_D0_5V: J1.B26 (CHR_D0), RN13.1 (R1.1)
/PPU_D1_3.3V: U5.22 (Q1), U9.20 (B1)
/PPU_D1_5V: J1.B27 (CHR_D1), RN13.2 (R2.1)
/PPU_D2_3.3V: U5.23 (Q2), U9.19 (B2)
/PPU_D2_5V: J1.B28 (CHR_D2), RN13.3 (R3.1)
/PPU_D3_3.3V: U5.25 (Q3), U9.18 (B3)
/PPU_D3_5V: J1.B29 (CHR_D3), RN13.4 (R4.1)
/PPU_D4_3.3V: U5.29 (Q7), U9.14 (B7)
/PPU_D4_5V: J1.A30 (CHR_D4), RN14.4 (R4.1)
/PPU_D5_3.3V: U5.28 (Q6), U9.15 (B6)
/PPU_D5_5V: J1.A29 (CHR_D5), RN14.3 (R3.1)
/PPU_D6_3.3V: U5.27 (Q5), U9.16 (B5)
/PPU_D6_5V: J1.A28 (CHR_D6), RN14.2 (R2.1)
/PPU_D7_3.3V: U5.26 (Q4), U9.17 (B4)
/PPU_D7_5V: J1.A27 (CHR_D7), RN14.1 (R1.1)
/PPU_RD_3.3V: U1.20 (IO1_20/GCLK1), U7.47 (1A0)
/PPU_RD_5V: J1.B17 (CHR_OE), RN9.1 (R1.1)
/PPU/A13_3.3V: RN8.2 (R2.1), U1.107 (IO3_107)
/PPU/A13_5V: J1.A19 (CHR/A13), RN8.7 (R2.2)
/PPU/RD_M: U1.12 (IO1_12), U5.32 (~OE), U9.2 (DIR)
/PPU/WR_3.3V: RN8.4 (R4.1), U1.105 (IO3_105)
/PPU/WR_M: U1.3 (IO1_3), U5.5 (~WE)
/RESET_DETECT: C12.1, D1.1 (K), R3.1, U1.61 (IO4_61/DEV_CLRn)
/SRAM/CE: R2.2, U1.27 (IO1_27)
/SRAM/OE: U1.28 (IO1_28), U4.22 (~OE)
/SRAM/WE: R4.2, U1.29 (IO1_29), U4.27 (~WE)
/TCK: J2.5, U1.35 (TCK)
/TDI: J2.4, U1.34 (TDI)
/TDO: J2.6, U1.36 (TDO)
/TMS: J2.3, U1.33 (TMS)
//ROMSEL_3.3V: RN7.3 (R3.1), U1.91 (IO3_91/GCLK3)
//ROMSEL_5V: J1.A14 (PRG/CE), RN7.6 (R3.2)
GND: BT1.2 (-), C1.2, C2.2, C3.2, C4.2, C5.2, C6.2, C7.2, C8.2, C9.2, C10.2, C11.2, C12.2, C13.2, C14.2, C15.2, C16.2, C17.2, C18.2, C19.2, C20.2, C21.2, C22.2, C23.2, C24.2, C25.2, C26.2, C27.2, C28.2, J1.B1 (GND), J1.B16 (GND), J2.2, R3.2, RN4.4 (R4.1), RN4.5 (R4.2), RN7.1 (R1.1), RN7.8 (R1.2), RN8.1 (R1.1), RN8.8 (R1.2), RN12.4 (R4.1), RN12.5 (R4.2), U1.10 (GNDIO), U1.17 (GNDINT), U1.26 (GNDIO), U1.47 (GNDIO), U1.54 (GNDINT), U1.65 (GNDIO), U1.83 (GNDIO), U1.92 (GNDINT), U1.99 (GNDIO), U1.115 (GNDIO), U1.128 (GNDINT), U1.135 (GNDIO), U2.1 (GND), U3.33 (GND), U3.52 (GND), U3.53 (BYTE#), U4.14 (VSS), U5.24 (GND), U5.30 (~CS1), U6.1 (1DIR), U6.4 (GND), U6.10 (GND), U6.15 (GND), U6.21 (GND), U6.23 (2B7), U6.24 (2DIR), U6.28 (GND), U6.34 (GND), U6.39 (GND), U6.45 (GND), U7.1 (1DIR), U7.4 (GND), U7.10 (GND), U7.15 (GND), U7.21 (GND), U7.23 (2B7), U7.24 (2DIR), U7.25 (2~OE), U7.28 (GND), U7.34 (GND), U7.39 (GND), U7.45 (GND), U7.48 (1~OE), U8.11 (GND_2), U8.12 (GND), U8.13 (GND_3), U9.11 (GND_2), U9.12 (GND), U9.13 (GND_3), U9.22 (~OE)
unnamed: BT1.1 (+), D2.2 (A)
unnamed: J1.A17 (CHR/WR), RN8.5 (R4.2)
unnamed: J1.A18 (CIRAM/CS), RN8.6 (R3.2)
unnamed: J1.A2 (M2), RN7.5 (R4.2)
unnamed: J1.A15 (SND_IN), J1.A16 (SND_OUT)
unnamed: RN1.8 (R1.2), U6.2 (1B0)
unnamed: RN1.7 (R2.2), U6.3 (1B1)
unnamed: RN1.6 (R3.2), U6.5 (1B2)
unnamed: RN1.5 (R4.2), U6.6 (1B3)
unnamed: RN2.8 (R1.2), U6.8 (1B4)
unnamed: RN2.7 (R2.2), U6.9 (1B5)
unnamed: RN2.6 (R3.2), U6.11 (1B6)
unnamed: RN2.5 (R4.2), U6.12 (1B7)
unnamed: RN3.8 (R1.2), U6.13 (2B0)
unnamed: RN3.7 (R2.2), U6.14 (2B1)
unnamed: RN3.6 (R3.2), U6.16 (2B2)
unnamed: RN3.5 (R4.2), U6.17 (2B3)
unnamed: RN4.8 (R1.2), U6.19 (2B4)
unnamed: RN4.7 (R2.2), U6.20 (2B5)
unnamed: RN4.6 (R3.2), U6.22 (2B6)
unnamed: RN5.8 (R1.2), U8.3 (A0)
unnamed: RN5.7 (R2.2), U8.4 (A1)
unnamed: RN5.6 (R3.2), U8.5 (A2)
unnamed: RN5.5 (R4.2), U8.6 (A3)
unnamed: RN6.8 (R1.2), U8.7 (A4)
unnamed: RN6.7 (R2.2), U8.8 (A5)
unnamed: RN6.6 (R3.2), U8.9 (A6)
unnamed: RN6.5 (R4.2), U8.10 (A7)
unnamed: RN9.8 (R1.2), U7.2 (1B0)
unnamed: RN9.7 (R2.2), U7.3 (1B1)
unnamed: RN9.6 (R3.2), U7.5 (1B2)
unnamed: RN9.5 (R4.2), U7.6 (1B3)
unnamed: RN10.8 (R1.2), U7.8 (1B4)
unnamed: RN10.7 (R2.2), U7.9 (1B5)
unnamed: RN10.6 (R3.2), U7.11 (1B6)
unnamed: RN10.5 (R4.2), U7.12 (1B7)
unnamed: RN11.8 (R1.2), U7.13 (2B0)
unnamed: RN11.7 (R2.2), U7.14 (2B1)
unnamed: RN11.6 (R3.2), U7.16 (2B2)
unnamed: RN11.5 (R4.2), U7.17 (2B3)
unnamed: RN12.8 (R1.2), U7.19 (2B4)
unnamed: RN12.7 (R2.2), U7.20 (2B5)
unnamed: RN12.6 (R3.2), U7.22 (2B6)
unnamed: RN13.8 (R1.2), U9.3 (A0)
unnamed: RN13.7 (R2.2), U9.4 (A1)
unnamed: RN13.6 (R3.2), U9.5 (A2)
unnamed: RN13.5 (R4.2), U9.6 (A3)
unnamed: RN14.8 (R1.2), U9.7 (A4)
unnamed: RN14.7 (R2.2), U9.8 (A5)
unnamed: RN14.6 (R3.2), U9.9 (A6)
unnamed: RN14.5 (R4.2), U9.10 (A7)
unnamed: C14.1, R1.1, R2.1, U4.20 (~CE)

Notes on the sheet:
Solder JP1 for FRAM
For SRAM 62256

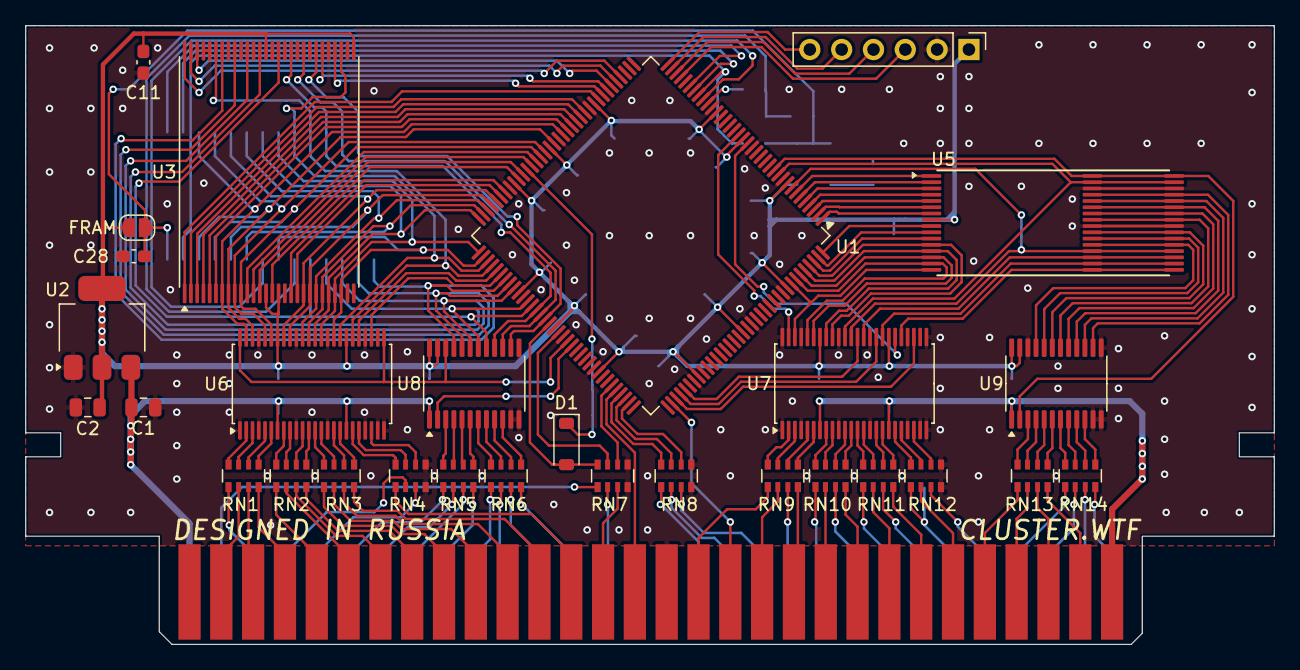
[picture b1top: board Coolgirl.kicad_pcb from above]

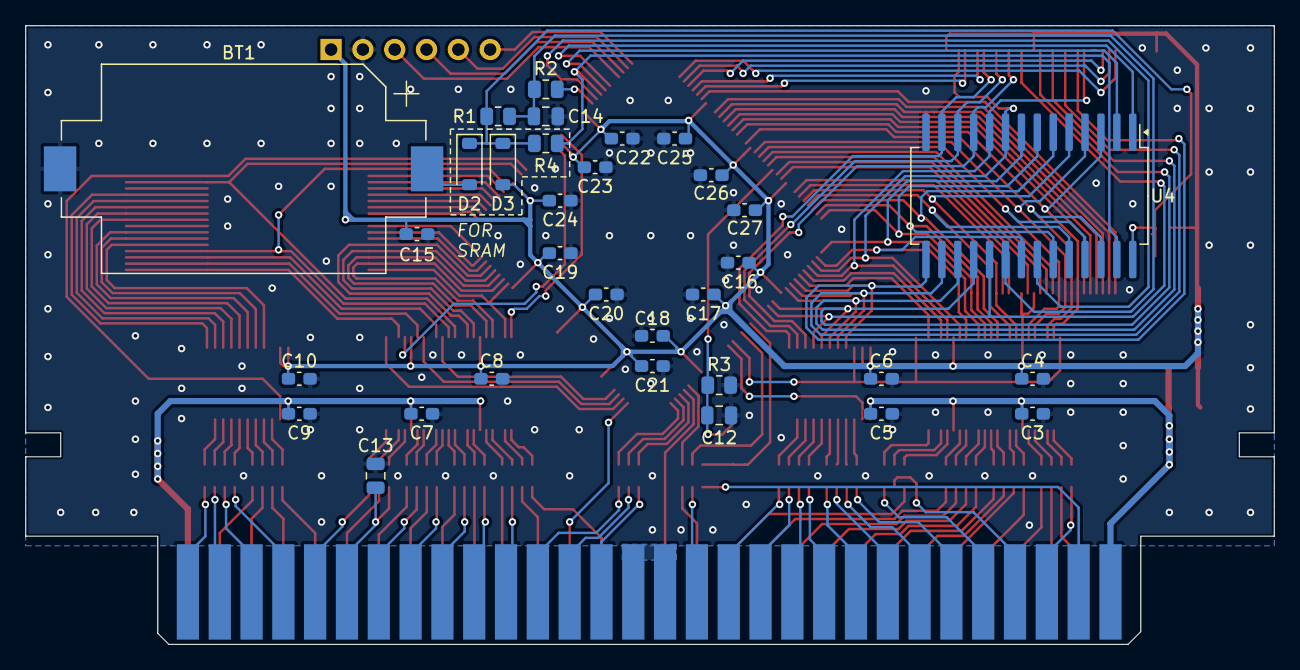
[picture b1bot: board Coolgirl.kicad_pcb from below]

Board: 2 copper layers, 99.7 x 49.4 mm, 62 parts (32 on the bottom side), 199 nets.

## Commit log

2025-02-20 rev6.4 KiCad project
